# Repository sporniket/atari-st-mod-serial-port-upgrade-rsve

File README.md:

# The RSVE serial port mod for the Atari ST

_Starting from after version 1.0.0, the project is migrated to Kicad 6_

> [WARNING] Please read carefully this note before using this project. It contains important facts.

Content

1. What is **The RSVE serial port mod for the Atari ST**, and when to use it ?
2. What should you know before using **The RSVE serial port mod for the Atari ST** ?
3. How to use **The RSVE serial port mod for the Atari ST** ?
4. Known issues
5. Miscellanous

## 1. What is **The RSVE serial port mod for the Atari ST**, and when to use it ?

**The RSVE serial port mod for the Atari ST** is a remake of the 'RSVE' serial port upgrade for the Atari ST, that allows to use far higher speed than the stock 19.2 kbps of an unmodded computer.

This project started from [this thread at exxosforum](https://exxosforum.co.uk/forum/viewtopic.php?f=29&t=5926) and the latest pages details what has been attempted to make it work with BBS Express (tldr : at the time of writing, it works at 38kbps, but then incoming calls at slower speed does not works).

### Licence

**The RSVE serial port mod for the Atari ST** is published under the Creative Commons CC0 license. You can find a copy of the licence there : https://creativecommons.org/publicdomain/zero/1.0/legalcode

You can copy, modify, distribute and perform the work, even for commercial purposes, all without asking permission.

**The RSVE serial port mod for the Atari ST** is distributed in the hope that it will be useful, but WITHOUT ANY WARRANTY; without even the implied warranty of MERCHANTABILITY or FITNESS FOR A PARTICULAR PURPOSE.

### Release notes

#### v1.0.0

* Initial release (gerbers, schematics). The tests performed in the thread at exxosforums shows that it works.

## 2. What should you know before using **The RSVE serial port mod for the Atari ST** ?

**The RSVE serial port mod for the Atari ST** is made using Kicad 6. _Up to version 1.0.0 included, it was made with Kicad 5_

The mod contains a GAL16V8 that has to be programmed. The JED file, along with the source, can be found in the [reference folder](./reference/rsve/) :

* [JED file](./reference/rsve/RSVE_GAL.JED)
* [Source of the JED](./reference/rsve/RSVE_GAL.TXT)

> Do not use **The RSVE serial port mod for the Atari ST** if this project is not suitable for your project.

## 3. How to use **The RSVE serial port mod for the Atari ST** ?

### From releases

A release contains the schematics and gerbers files.

### From sources

To get the latest available work, one must clone the git repository.

	git clone https://github.com/sporniket/atari-st-mod-serial-port-upgrade-rsve.git

Then, open the project with Kicad 5

## 4. Known issues
See the [project issues](https://github.com/sporniket/atari-st-mod-serial-port-upgrade-rsve/issues) page.

## 5. Miscellanous

### The original description of the mod

See the content of [`reference/rsve`](./reference/rsve) folder.

### The installation guide

See [the quick installation guide](./reference/quick-installation-guide/rsve-quick-install-guide.pdf)

### Report issues
Use the [project issues](https://github.com/sporniket/atari-st-mod-serial-port-upgrade-rsve/issues) page.

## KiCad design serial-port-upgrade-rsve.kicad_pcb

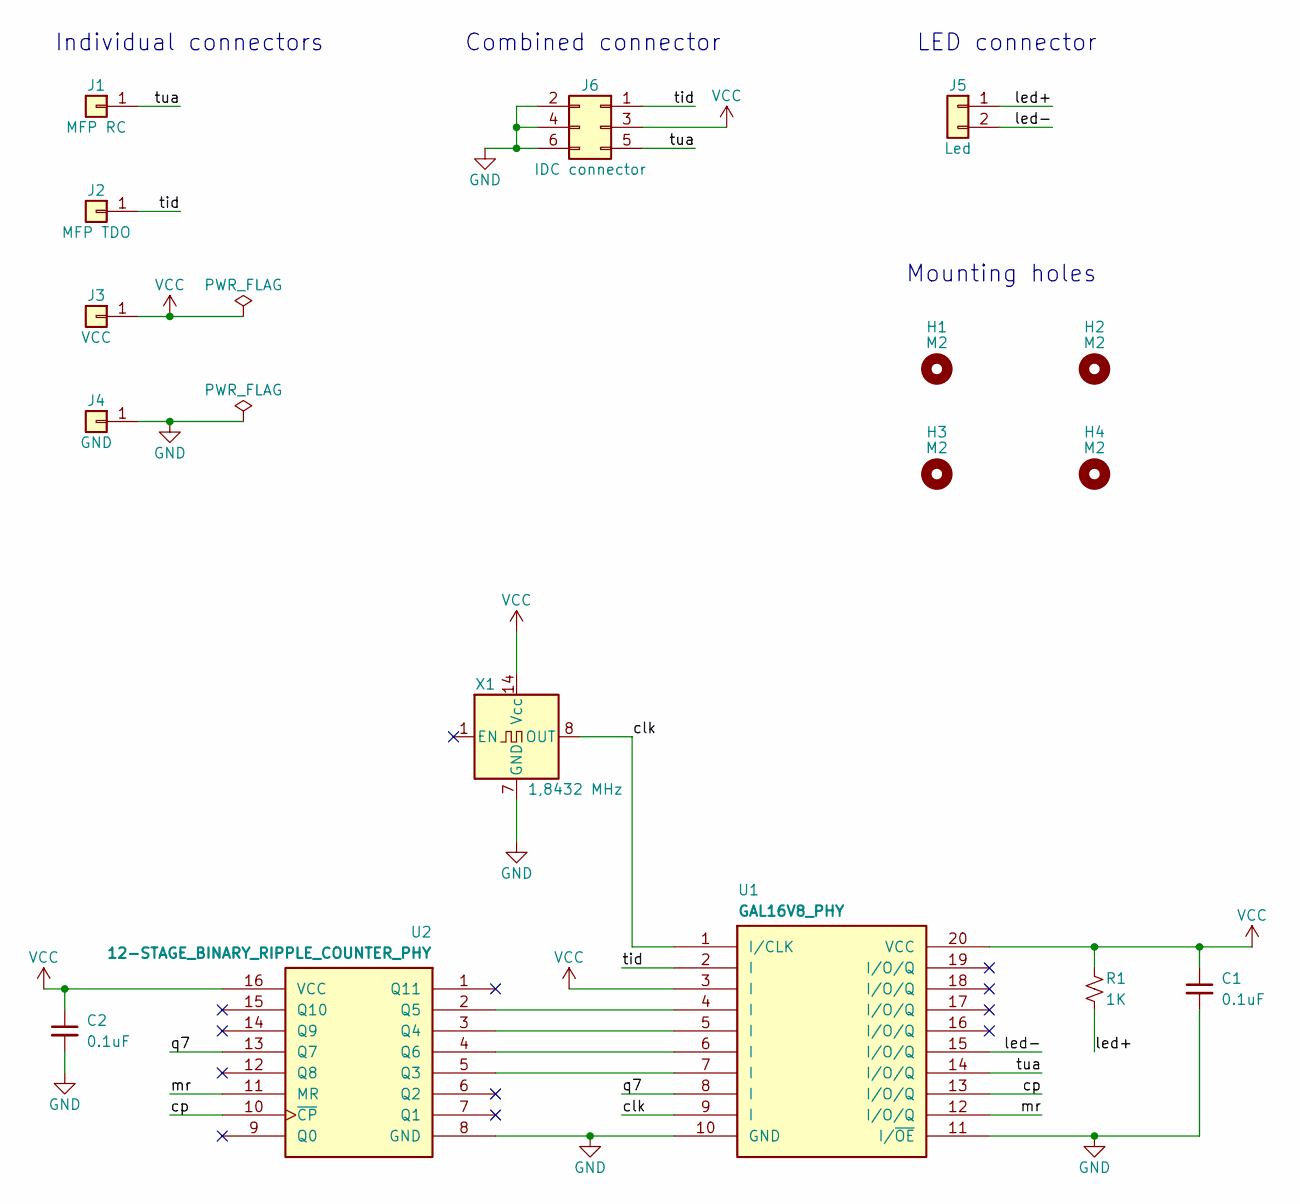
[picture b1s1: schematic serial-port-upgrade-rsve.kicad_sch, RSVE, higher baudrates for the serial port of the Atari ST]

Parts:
C1, C2: 0.1uF; Passive_THT_capacitor_mlcc_W2.54mm_L7.62mm
H1, H2, H3, H4: M2; MountingHole_2.2mm_M2
J1: MFP RC; PinHeader_1x01_P2.54mm_Vertical
J2: MFP TDO; PinHeader_1x01_P2.54mm_Vertical
J3: VCC; PinHeader_1x01_P2.54mm_Vertical
J4: GND; PinHeader_1x01_P2.54mm_Vertical
J5: Led; PinHeader_1x02_P2.54mm_Vertical
J6: IDC connector; IDC-Header_2x03_P2.54mm_Horizontal
R1: 1K; Passive_THT_resistor_W2.54mm_L10.16mm
U1: GAL16V8_PHY; DIP-20_W7.62mm_LongPads
U2: 12-STAGE_BINARY_RIPPLE_COUNTER_PHY; DIP-16_W7.62mm_LongPads
X1: 1,8432 MHz; Oscillator_DIP-14

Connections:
/clk: U1.1 (I/CLK), U1.9 (I), X1.8 (OUT)
/cp: U1.13 (I/O/Q), U2.10 (~CP)
/led+: J5.1, R1.2
/led-: J5.2, U1.15 (I/O/Q)
/mr: U1.12 (I/O/Q), U2.11 (MR)
/q7: U1.8 (I), U2.13 (Q7)
/tid: J2.1, J6.1, U1.2 (I)
/tua: J1.1, J6.5, U1.14 (I/O/Q)
GND: C1.2, C2.2, J4.1, J6.2, J6.4, J6.6, U1.10 (GND), U1.11 (I/~OE), U2.8 (GND), X1.7 (GND)
unnamed: U1.4 (I), U2.2 (Q5)
unnamed: U1.5 (I), U2.3 (Q4)
unnamed: U1.6 (I), U2.4 (Q6)
unnamed: U1.7 (I), U2.5 (Q3)
VCC: C1.1, C2.1, J3.1, J6.3, R1.1, U1.3 (I), U1.20 (VCC), U2.16 (VCC), X1.14 (Vcc)

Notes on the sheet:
Mounting holes
Combined connector
Individual connectors
LED connector

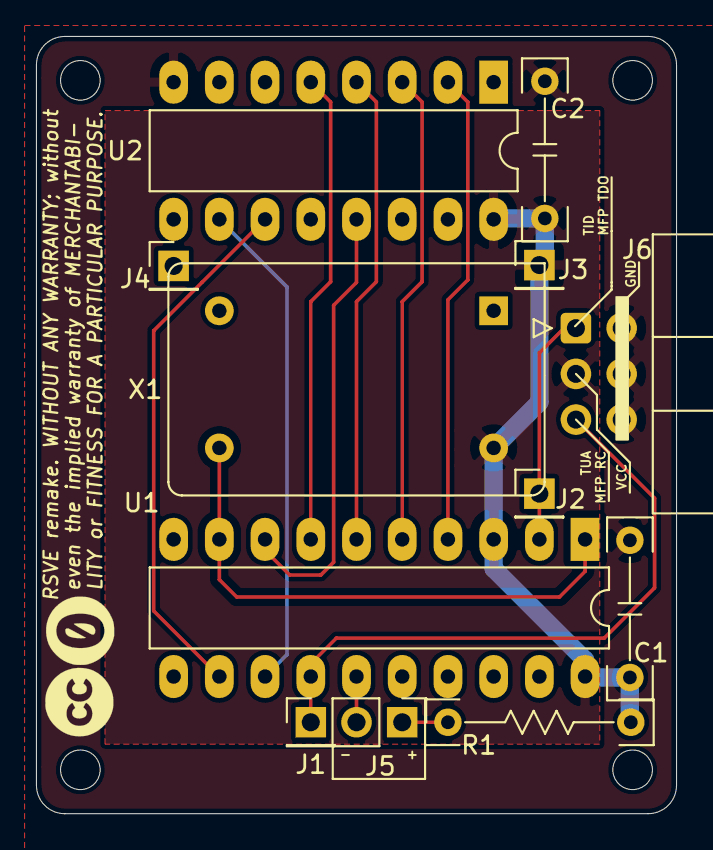
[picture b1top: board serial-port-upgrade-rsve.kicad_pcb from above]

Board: 4 copper layers, 35.6 x 43.2 mm, 16 parts (0 on the bottom side), 14 nets.

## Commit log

2022-07-10 added my typical gitignore
2022-07-10 update generated symbols
2022-09-30 Add a template for the project README, with instruction to change some placeholders with values specific to the new project
2022-09-30 update kicad-symbols-generated
2022-10-14 remove submodule kicad-symbols-generated
2022-10-14 use the release libs of kicad-symbols-generated
2022-10-14 update README : build step no more needed
2022-10-21 update footprint libs
2022-11-04 update submodules
2022-11-07 init README
2022-11-07 add license file
2022-11-07 copy of the original mod for reference, some file converted into modern format
2022-11-07 try to fix table formatting
2022-11-07 try to fix table formatting #2
2022-11-07 fixed table formatting
2022-11-08 done schematics
2022-11-09 associate footprints, start PCB
2022-11-09 added reference layout, place components
2022-11-09 setup pcb stack
2022-11-09 done routing
2022-11-09 added IDC connector, adjusted reference label position
2022-11-09 licence logo, title and disclaimer on PCB
2022-11-09 added mounting hole
2022-11-10 silkscreen : replace MFP pin number mentions (DIP 48 specific) by pin names
2022-11-10 last tweaks on the silkscreen : repository url, notice/disclaimer on the front
2022-11-10 some vanity shots simulations for the readme
2022-11-10 notice/disclaimer sizing
2022-11-10 schematic : change 'piggy back' to 'individuals', and reorganize layout
2022-11-10 pcb : cartridge setup
2022-11-10 pcb : settings for plotting the silk screen on pdf
2022-11-10 pcb : settings for exporting gerbers
2023-01-10 quick installation guide libre office source + pdf
2023-01-10 update README to mention exxosforum original thread and current status in relation with BBS express
2023-01-10 update installation guide, complete main README
2023-01-10 mention the presence of a GAL16V8
2023-02-07 Resolves #1 : Migrate to Kicad 6
